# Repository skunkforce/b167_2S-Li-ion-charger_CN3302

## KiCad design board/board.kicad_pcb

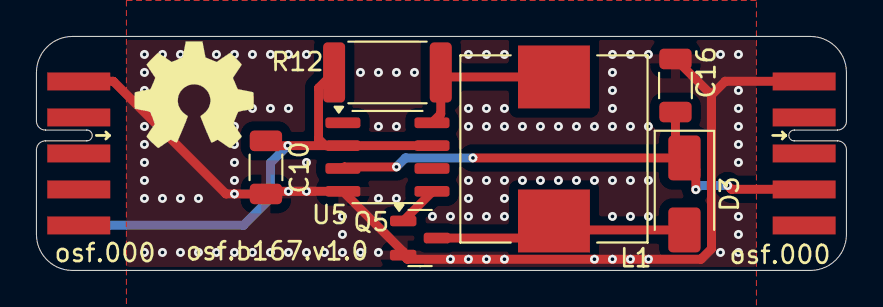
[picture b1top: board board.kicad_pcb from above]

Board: 2 copper layers, 45.0 x 13.0 mm, 10 parts (0 on the bottom side), 6 nets.

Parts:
C10, C16: 10uF; C_1206_3216Metric
D3: SS34; D_SMA
J1: 022_battery_cells; on_edge_2x05_host
J2: 000_3.3v_5v; on_edge_2x05_device
L1: 10uH; L_Wuerth_HCI-1040
LOGO1: Logo_Open_Hardware_Small; OSHW-Symbol_6.7x6mm_SilkScreen
Q5: HXY3404M; SOT-23
R12: 80mR; R_2512_6332Metric
U5: CN3302; SOIC-8_3.9x4.9mm_P1.27mm

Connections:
/implementation/BATT: C16.1, D3.1 (K), J1.4 (C2+C3-), U5.3 (BATT)
/implementation/CE: C10.1, J2.10 (5V), R12.2, U5.2 (CE), U5.7 (VIN)
GND: C10.2, C16.2, J1.1 (GND), J2.1 (GND), Q5.2 (S), U5.4 (GND)
unnamed: D3.2 (A), L1.2, Q5.3 (D)
unnamed: Q5.1 (G), U5.5 (LDRV)
unnamed: L1.1, R12.1, U5.8 (CSN)

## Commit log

2025-04-30 initial
2025-04-30 fixed on_edge connector placement
